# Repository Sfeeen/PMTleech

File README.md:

# 🚀 PMT Leech
#### A Parallel Memory Transactions Monitor

**PMT Leech** is a hardware + software tool that lets you monitor live memory accesses from a CPU to an external parallel memory chip.  
It streams transactions in real-time, while giving you full control over the system clock — allowing **pausing, stepping, and instruction-level debugging**.

---

## 🔧 When Should You Use PMT Leech?

PMT Leech is especially useful when working with **older electronic systems** that meet these two conditions:
- ✅ The system uses a **parallel memory chip** (like SRAM or EPROM)
- ✅ The CPU operates with an **external clock input**

---

## ⚙️ How It Works

By attaching PMT Leech to your memory chip (via clipper) and supplying your own clock signal to the CPU:
- You gain **live streaming** of memory transactions
- You can **pause or step** through firmware execution  
- You can **reverse engineer or debug** embedded firmware in a safe, controlled way

---

## 🧰 Hardware Overview

---

## 🖥️ Software Features

- 🧩 Configurable pinout: Supports 28, 30, or 32-pin chips
- 📡 Live recording of transactions (up to 70kHz)
- 🎨 Interactive memory viewer with color-coded highlights
- ⏱ Step by **clock** or **instruction**
- 🧠 Detect and label **foreign packets** (from other devices on the memory bus)
- 💾 Off-circuit memory read/write with chip socket

---

## 🎞️ Demo

---

## 📋 Requirements

### ✅ Memory Chip
- Parallel bus
- ≤ 8-bit data
- ≤ 18 address lines
- 5V compatible (or use 330Ω series resistors)

### ✅ CPU
- Must allow external clock input
- 5V compatible (or 330Ω resistors)

### ⚠️ Note on Timing
The CPU will be **underclocked** (e.g., 8 MHz → 50 kHz). This may affect peripherals like UART:
- Ex: 9600 baud becomes ~60 baud — comms may break.

---

## 🧲 In-Circuit Clip Options

- [📄 3M Test Clip Brochure (PDF)](research/in%20circuit%20connection%20to%20chips/Test%20Clip%20Brochure%203M.pdf)

---

## 🧠 Supported Memory Types

- EEPROM
- EPROM
- SRAM — **especially valuable** for volatile firmware systems

💡 Many older systems used **SRAM for firmware** due to speed advantages. PMT Leech lets you read these **volatile** setups **without desoldering**.

---

## 🔍 Example Use Cases

- **Bypass password protection**: Record firmware transactions during password validation and discover comparison logic or values.
- **Firmware reverse engineering**: Step through opcode streams and infer instruction flow.
- **Brownout glitching**: Control timing to inject faults and analyze behavior.
  - Related project: [Siemens Advanced Operator Panel](https://github.com/Sfeeen/Siemens-Advanced-Operator-Panel)

---

## 🛠️ Hardware Revisions

### PMT Leech v2 (Current)

### PMT Leech v1 (Development Stage)

---

##

📧 **Contact**: `svenonderbeke [at] hotmail [dot] com`  
More info to be added soon.

---

### ☕ Support

If you’d like to support the development of PMT Leech, you can donate via Ko-fi:

## 🧪 Version

**Current Version:** `PMT Leech v2`

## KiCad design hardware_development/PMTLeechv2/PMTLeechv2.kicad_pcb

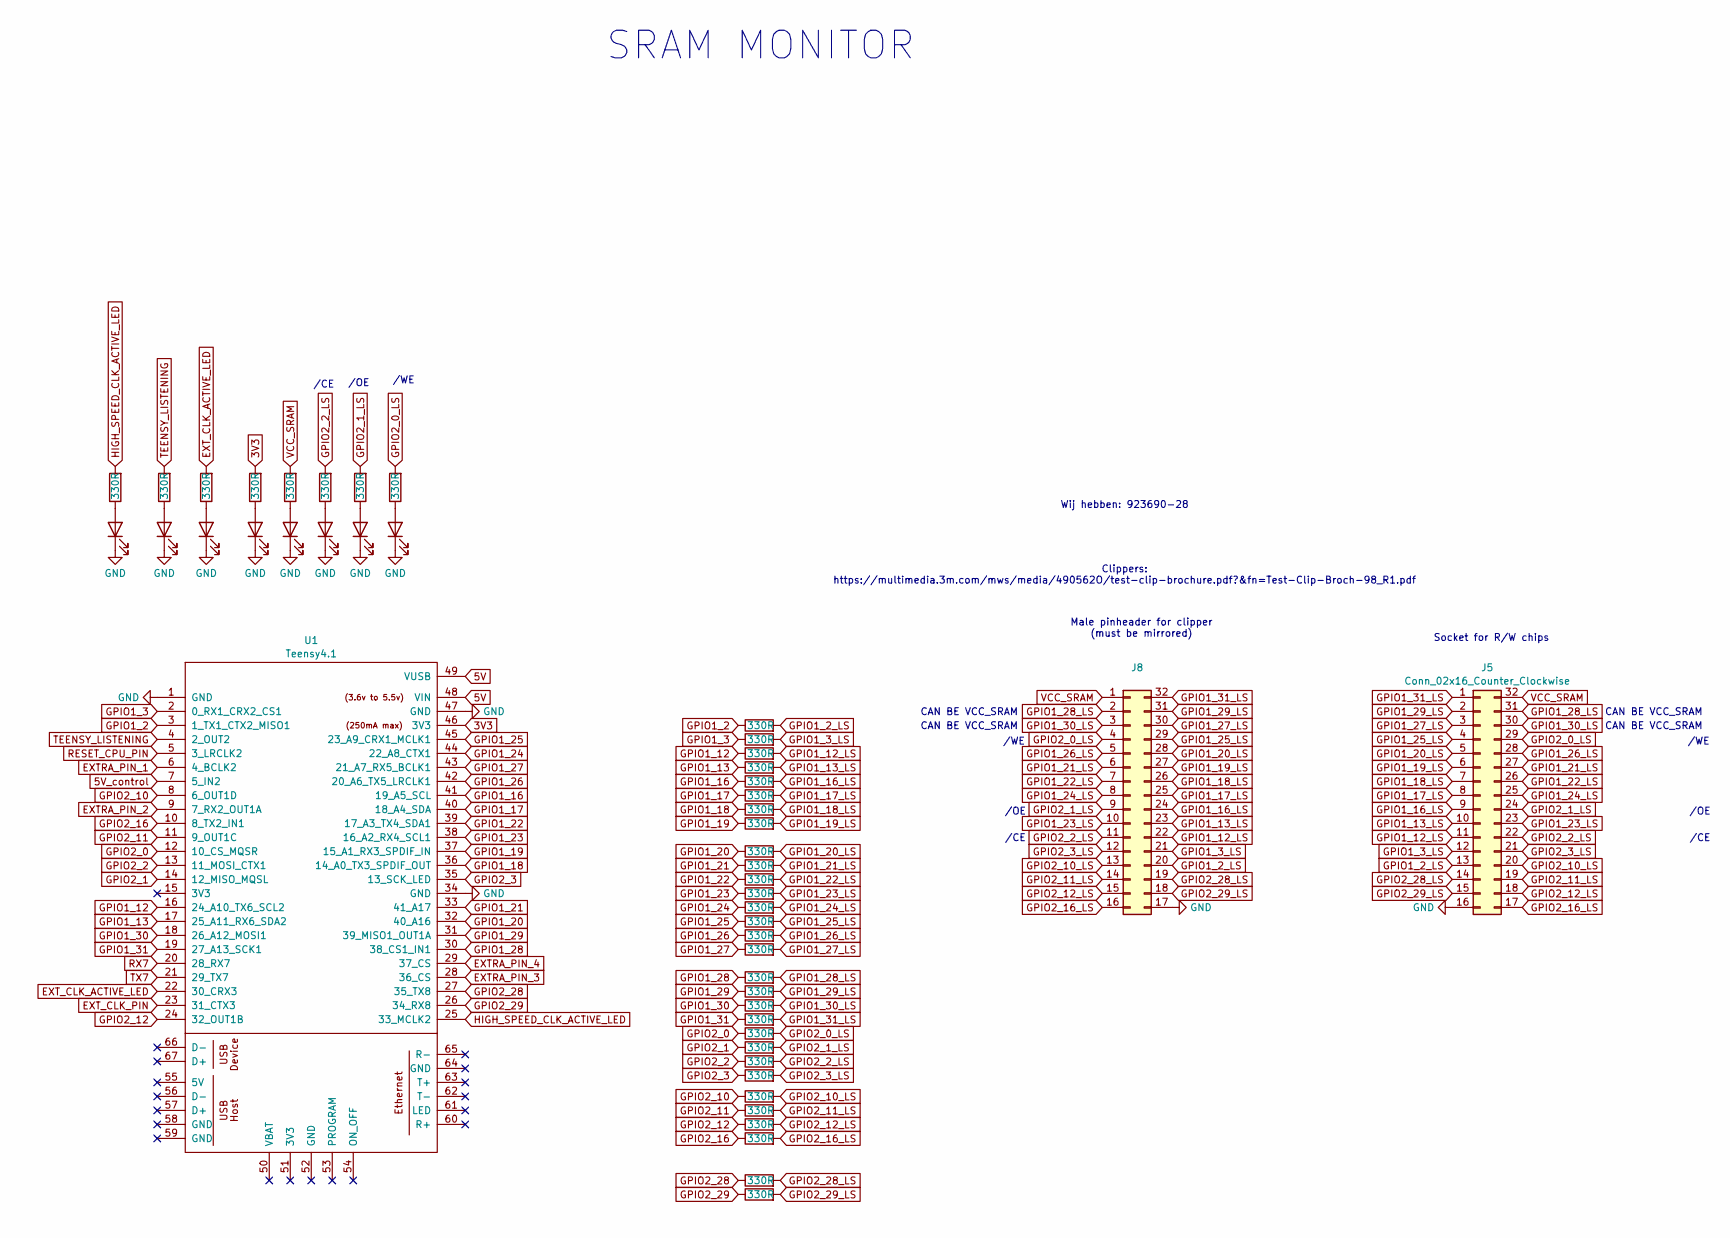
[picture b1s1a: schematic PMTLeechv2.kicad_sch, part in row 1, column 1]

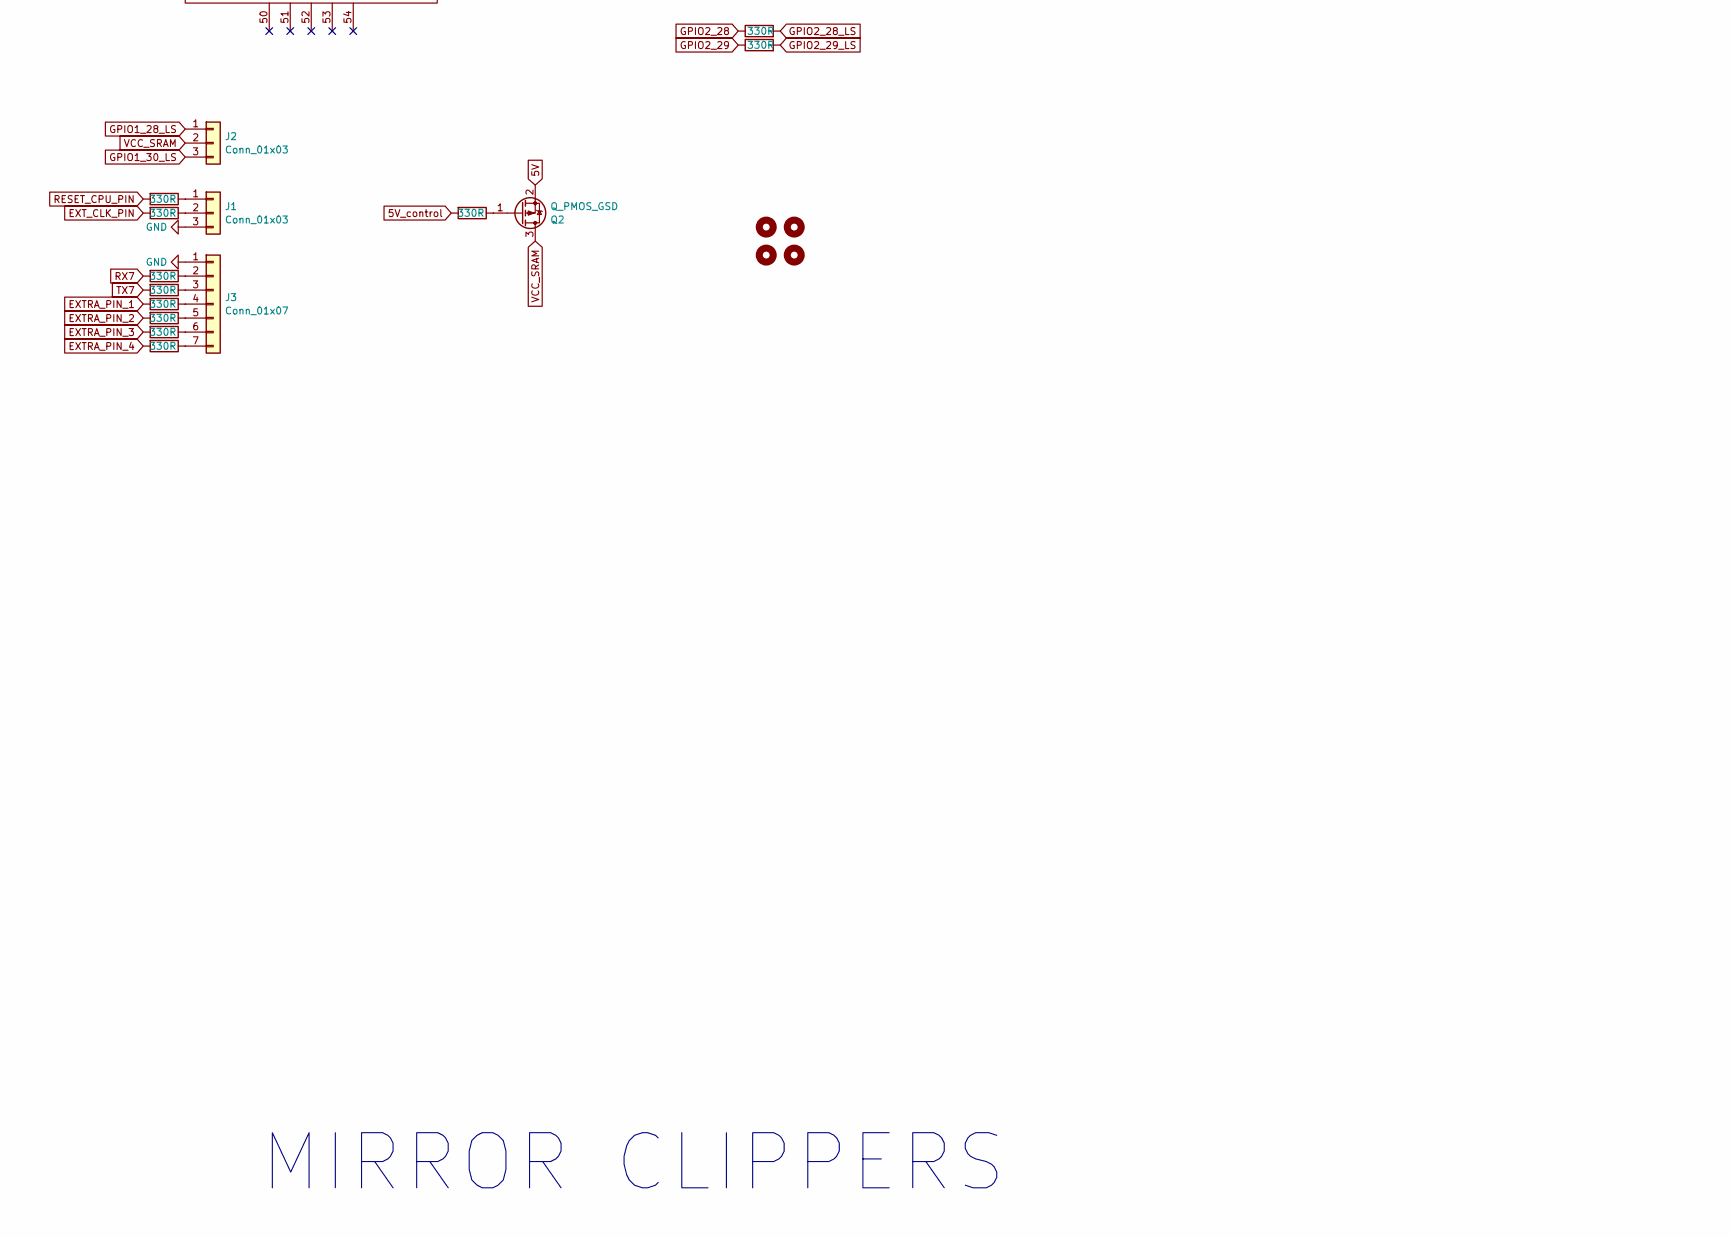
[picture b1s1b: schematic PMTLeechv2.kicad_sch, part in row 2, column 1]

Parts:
D1, D2, D3, D31, D32, D33, D34, D35: LED; LED_0805_2012Metric
H1, H2, H3, H4: MountingHole; MountingHole_3.2mm_M3
J1, J2: Conn_01x03; PinHeader_1x03_P2.54mm_Vertical
J3: Conn_01x07; PinHeader_1x07_P2.54mm_Vertical
J5: Conn_02x16_Counter_Clockwise; DIP-32_W15.24mm_Socket_LongPads
J8: Conn_02x16_Counter_Clockwise; PinHeader_2x16_P2.54mm_Vertical_clockwise
Q2: Q_PMOS_GSD; TSOT-23
R1, R2, R3, R4, R5, R6, R7, R8, R9, R10, R11, R12, R13, R14, R15, R16, R17, R18, R19, R20, R21, R22, R23, R24, R25, R26, R27, R28, R29, R30, R31, R32, R34, R35, R36, R37, R38, R39, R40, R41, R42, R43, R95, R96, R97, R98, R99: 330R; R_0603_1608Metric
U1: Teensy4.1; Teensy41

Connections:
3V3: R95.2, U1.46 (3V3)
5V: Q2.2 (S), U1.48 (VIN), U1.49 (VUSB)
5V_control: R30.2, U1.7 (5_IN2)
EXTRA_PIN_1: R37.2, U1.6 (4_BCLK2)
EXTRA_PIN_2: R42.2, U1.9 (7_RX2_OUT1A)
EXTRA_PIN_3: R38.2, U1.28 (36_CS)
EXTRA_PIN_4: R43.2, U1.29 (37_CS)
EXT_CLK_ACTIVE_LED: R34.2, U1.22 (30_CRX3)
EXT_CLK_PIN: R29.2, U1.23 (31_CTX3)
GND: D1.1 (K), D2.1 (K), D3.1 (K), D31.1 (K), D32.1 (K), D33.1 (K), D34.1 (K), D35.1 (K), J1.3, J3.1, J5.16, J8.17, U1.1 (GND), U1.34 (GND), U1.47 (GND)
GPIO1_2: R1.1, U1.3 (1_TX1_CTX2_MISO1)
GPIO1_2_LS: J5.13, J8.20, R1.2
GPIO1_3: R2.1, U1.2 (0_RX1_CRX2_CS1)
GPIO1_3_LS: J5.12, J8.21, R2.2
GPIO1_12: R3.1, U1.16 (24_A10_TX6_SCL2)
GPIO1_12_LS: J5.11, J8.22, R3.2
GPIO1_13: R4.1, U1.17 (25_A11_RX6_SDA2)
GPIO1_13_LS: J5.10, J8.23, R4.2
GPIO1_16: R5.1, U1.41 (19_A5_SCL)
GPIO1_16_LS: J5.9, J8.24, R5.2
GPIO1_17: R6.1, U1.40 (18_A4_SDA)
GPIO1_17_LS: J5.8, J8.25, R6.2
GPIO1_18: R7.1, U1.36 (14_A0_TX3_SPDIF_OUT)
GPIO1_18_LS: J5.7, J8.26, R7.2
GPIO1_19: R8.1, U1.37 (15_A1_RX3_SPDIF_IN)
GPIO1_19_LS: J5.6, J8.27, R8.2
GPIO1_20: R9.1, U1.32 (40_A16)
GPIO1_20_LS: J5.5, J8.28, R9.2
GPIO1_21: R10.1, U1.33 (41_A17)
GPIO1_21_LS: J5.27, J8.6, R10.2
GPIO1_22: R11.1, U1.39 (17_A3_TX4_SDA1)
GPIO1_22_LS: J5.26, J8.7, R11.2
GPIO1_23: R12.1, U1.38 (16_A2_RX4_SCL1)
GPIO1_23_LS: J5.23, J8.10, R12.2
GPIO1_24: R13.1, U1.44 (22_A8_CTX1)
GPIO1_24_LS: J5.25, J8.8, R13.2
GPIO1_25: R14.1, U1.45 (23_A9_CRX1_MCLK1)
GPIO1_25_LS: J5.4, J8.29, R14.2
GPIO1_26: R15.1, U1.42 (20_A6_TX5_LRCLK1)
GPIO1_26_LS: J5.28, J8.5, R15.2
GPIO1_27: R16.1, U1.43 (21_A7_RX5_BCLK1)
GPIO1_27_LS: J5.3, J8.30, R16.2
GPIO1_28: R17.1, U1.30 (38_CS1_IN1)
GPIO1_28_LS: J2.1, J5.31, J8.2, R17.2
GPIO1_29: R18.1, U1.31 (39_MISO1_OUT1A)
GPIO1_29_LS: J5.2, J8.31, R18.2
GPIO1_30: R19.1, U1.18 (26_A12_MOSI1)
GPIO1_30_LS: J2.3, J5.30, J8.3, R19.2
GPIO1_31: R20.1, U1.19 (27_A13_SCK1)
GPIO1_31_LS: J5.1, J8.32, R20.2
GPIO2_0: R21.1, U1.12 (10_CS_MQSR)
GPIO2_0_LS: J5.29, J8.4, R21.2, R99.2
GPIO2_1: R22.1, U1.14 (12_MISO_MQSL)
GPIO2_1_LS: J5.24, J8.9, R22.2, R98.2
GPIO2_2: R23.1, U1.13 (11_MOSI_CTX1)
GPIO2_2_LS: J5.22, J8.11, R23.2, R97.2
GPIO2_3: R24.1, U1.35 (13_SCK_LED)
GPIO2_3_LS: J5.21, J8.12, R24.2
GPIO2_10: R25.1, U1.8 (6_OUT1D)
GPIO2_10_LS: J5.20, J8.13, R25.2
GPIO2_11: R26.1, U1.11 (9_OUT1C)
GPIO2_11_LS: J5.19, J8.14, R26.2
GPIO2_12: R27.1, U1.24 (32_OUT1B)
GPIO2_12_LS: J5.18, J8.15, R27.2
GPIO2_16: R28.1, U1.10 (8_TX2_IN1)
GPIO2_16_LS: J5.17, J8.16, R28.2
GPIO2_28: R31.1, U1.27 (35_TX8)
GPIO2_28_LS: J5.14, J8.19, R31.2
GPIO2_29: R32.1, U1.26 (34_RX8)
GPIO2_29_LS: J5.15, J8.18, R32.2
HIGH_SPEED_CLK_ACTIVE_LED: R41.2, U1.25 (33_MCLK2)
unnamed: D1.2 (A), R34.1
unnamed: D2.2 (A), R35.1
unnamed: D3.2 (A), R41.1
unnamed: D31.2 (A), R95.1
unnamed: D32.2 (A), R96.1
unnamed: D33.2 (A), R97.1
unnamed: D34.2 (A), R98.1
unnamed: D35.2 (A), R99.1
unnamed: J1.1, R36.1
unnamed: J1.2, R29.1
unnamed: J3.2, R39.1
unnamed: J3.3, R40.1
unnamed: J3.4, R37.1
unnamed: J3.5, R42.1
unnamed: J3.6, R38.1
unnamed: J3.7, R43.1
unnamed: Q2.1 (G), R30.1
RESET_CPU_PIN: R36.2, U1.5 (3_LRCLK2)
RX7: R39.2, U1.20 (28_RX7)
TEENSY_LISTENING: R35.2, U1.4 (2_OUT2)
TX7: R40.2, U1.21 (29_TX7)
VCC_SRAM: J2.2, J5.32, J8.1, Q2.3 (D), R96.2

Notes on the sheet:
Wij hebben: 923690-28
CAN BE VCC_SRAM
/CE
/WE
SRAM MONITOR
MIRROR CLIPPERS
Clippers: https://multimedia.3m.com/mws/media/490562O/test-clip-brochure.pdf?&fn=Test-Clip-Broch-98_R1.pdf
Socket for R/W chips
/OE
Male pinheader for clipper (must be mirrored)

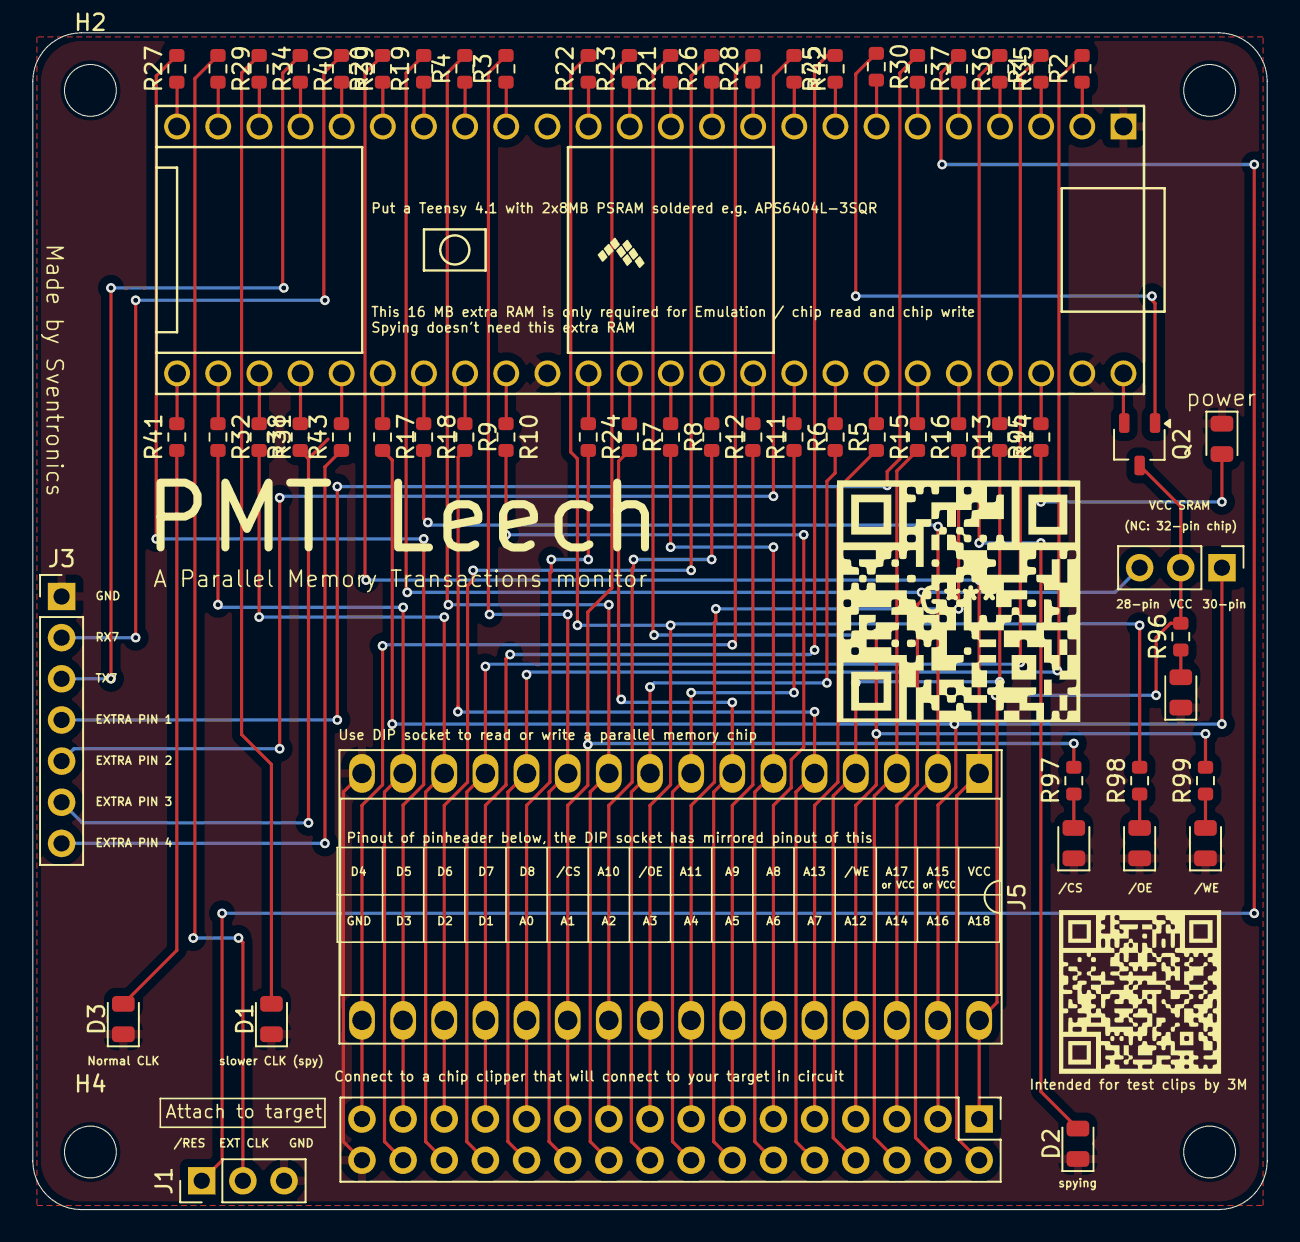
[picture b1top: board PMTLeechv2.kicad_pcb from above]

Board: 2 copper layers, 76.2 x 72.6 mm, 66 parts (0 on the bottom side), 93 nets.

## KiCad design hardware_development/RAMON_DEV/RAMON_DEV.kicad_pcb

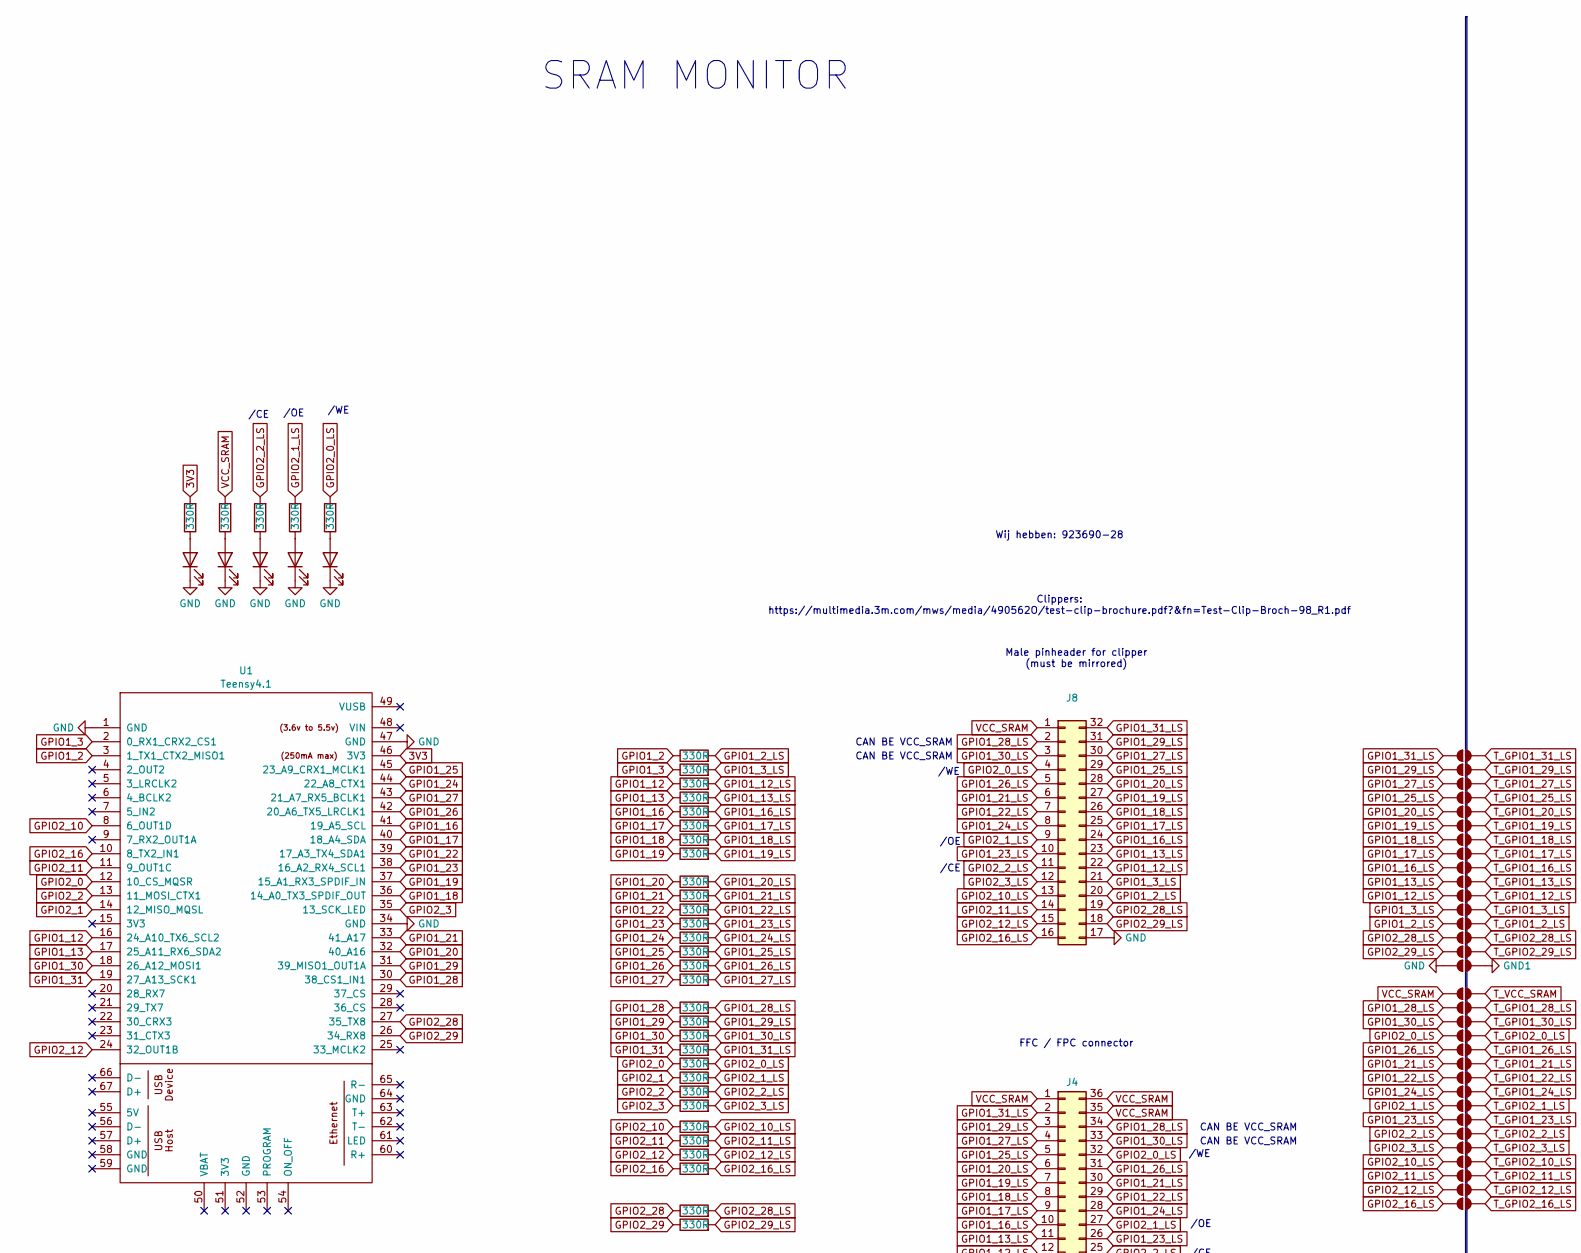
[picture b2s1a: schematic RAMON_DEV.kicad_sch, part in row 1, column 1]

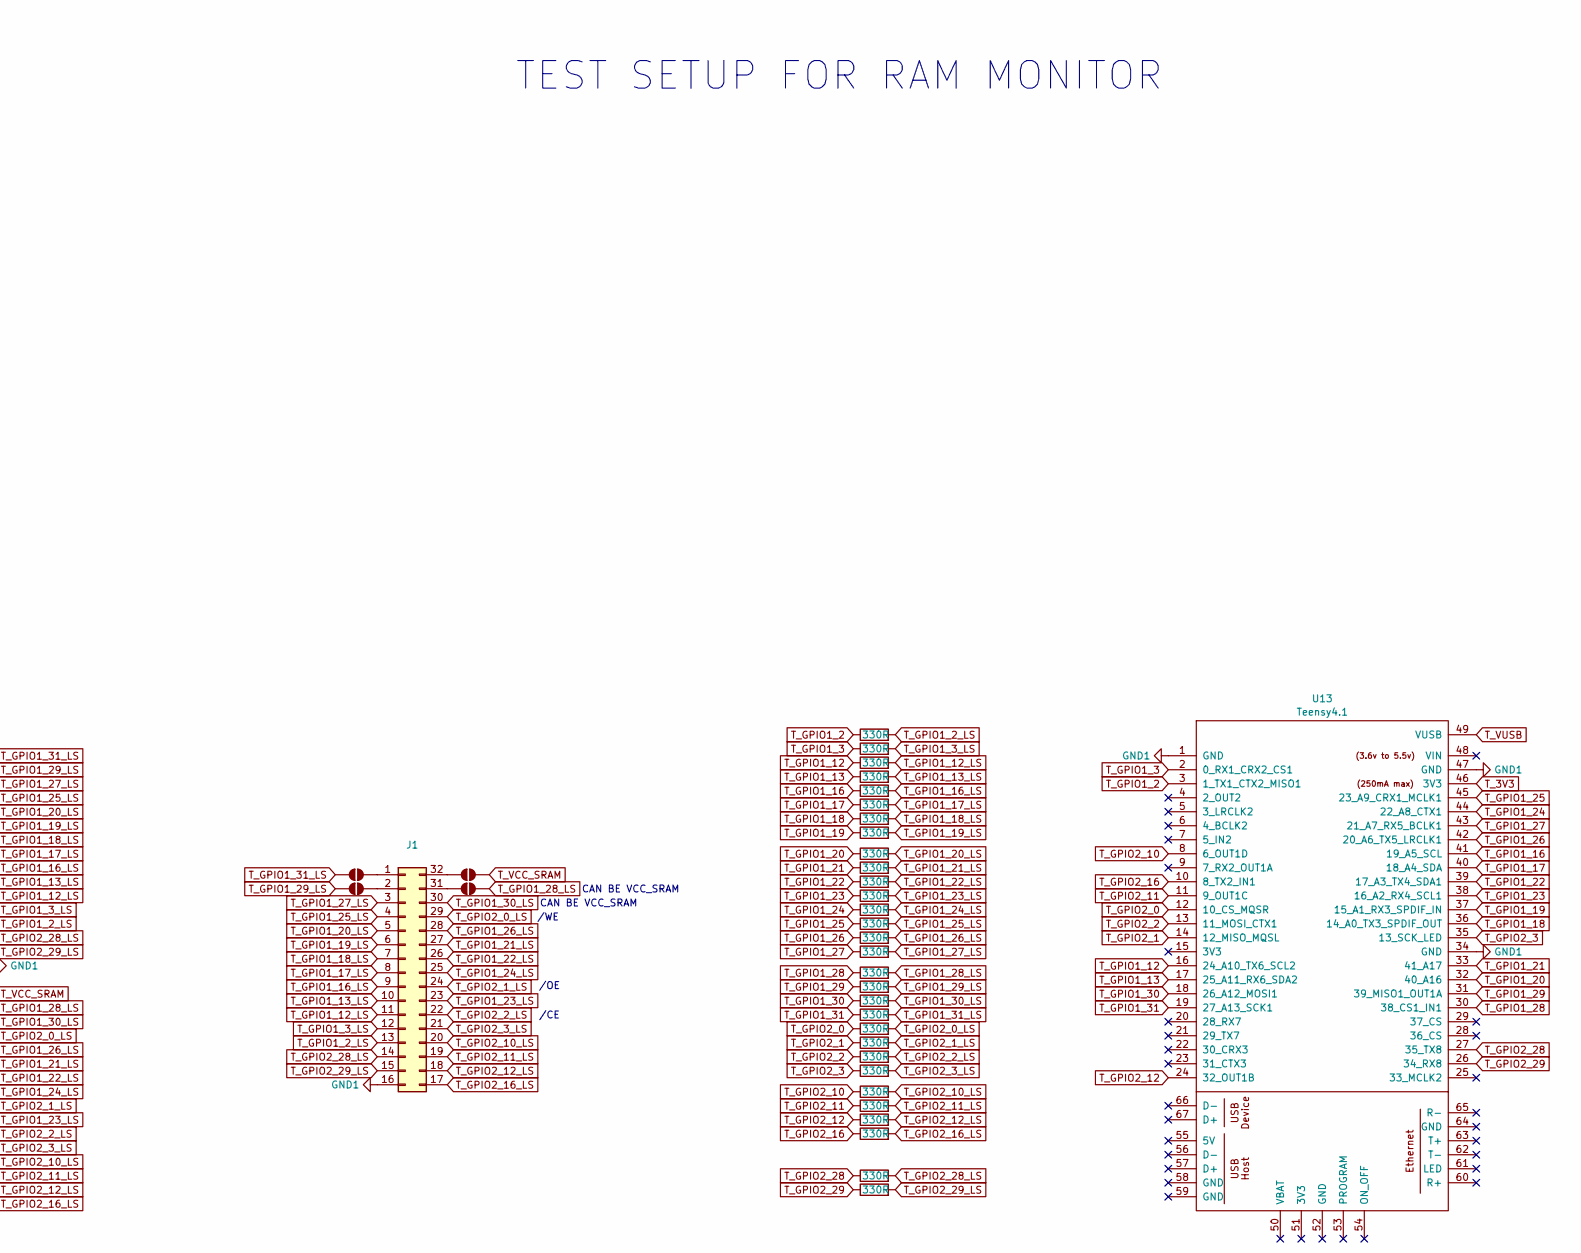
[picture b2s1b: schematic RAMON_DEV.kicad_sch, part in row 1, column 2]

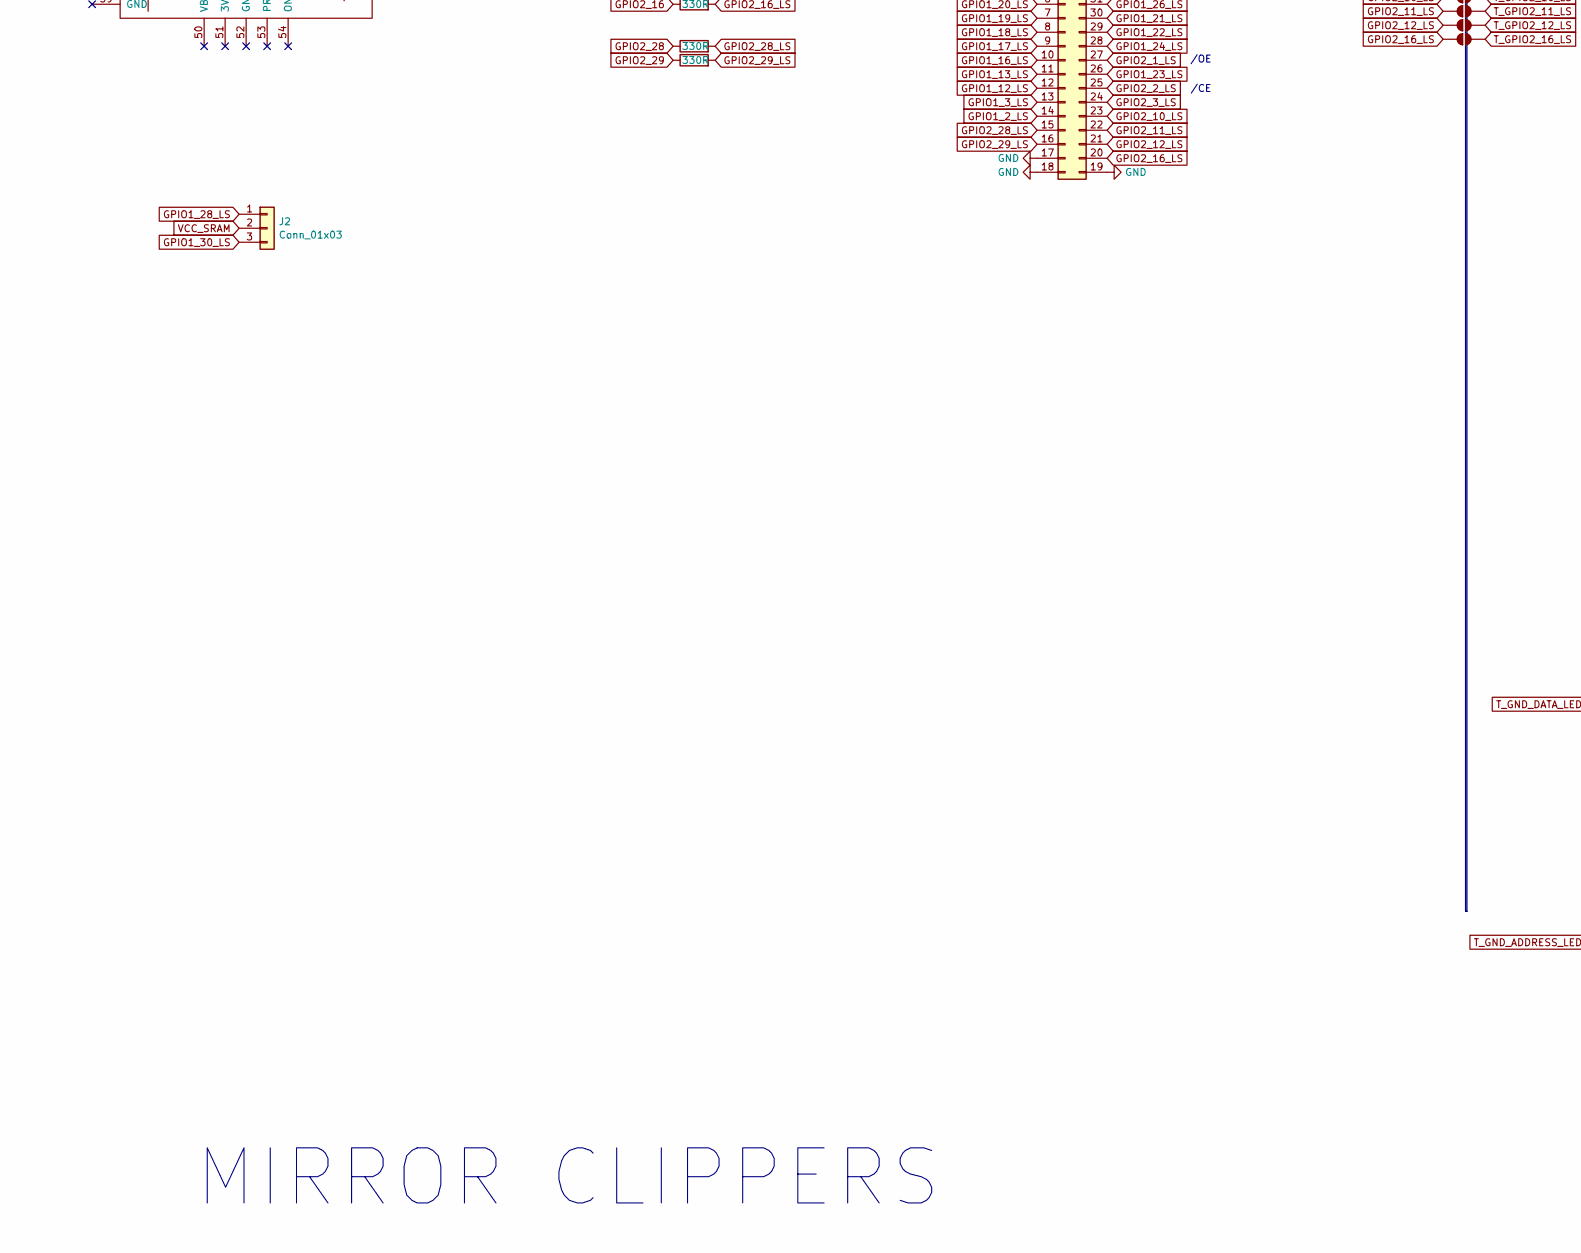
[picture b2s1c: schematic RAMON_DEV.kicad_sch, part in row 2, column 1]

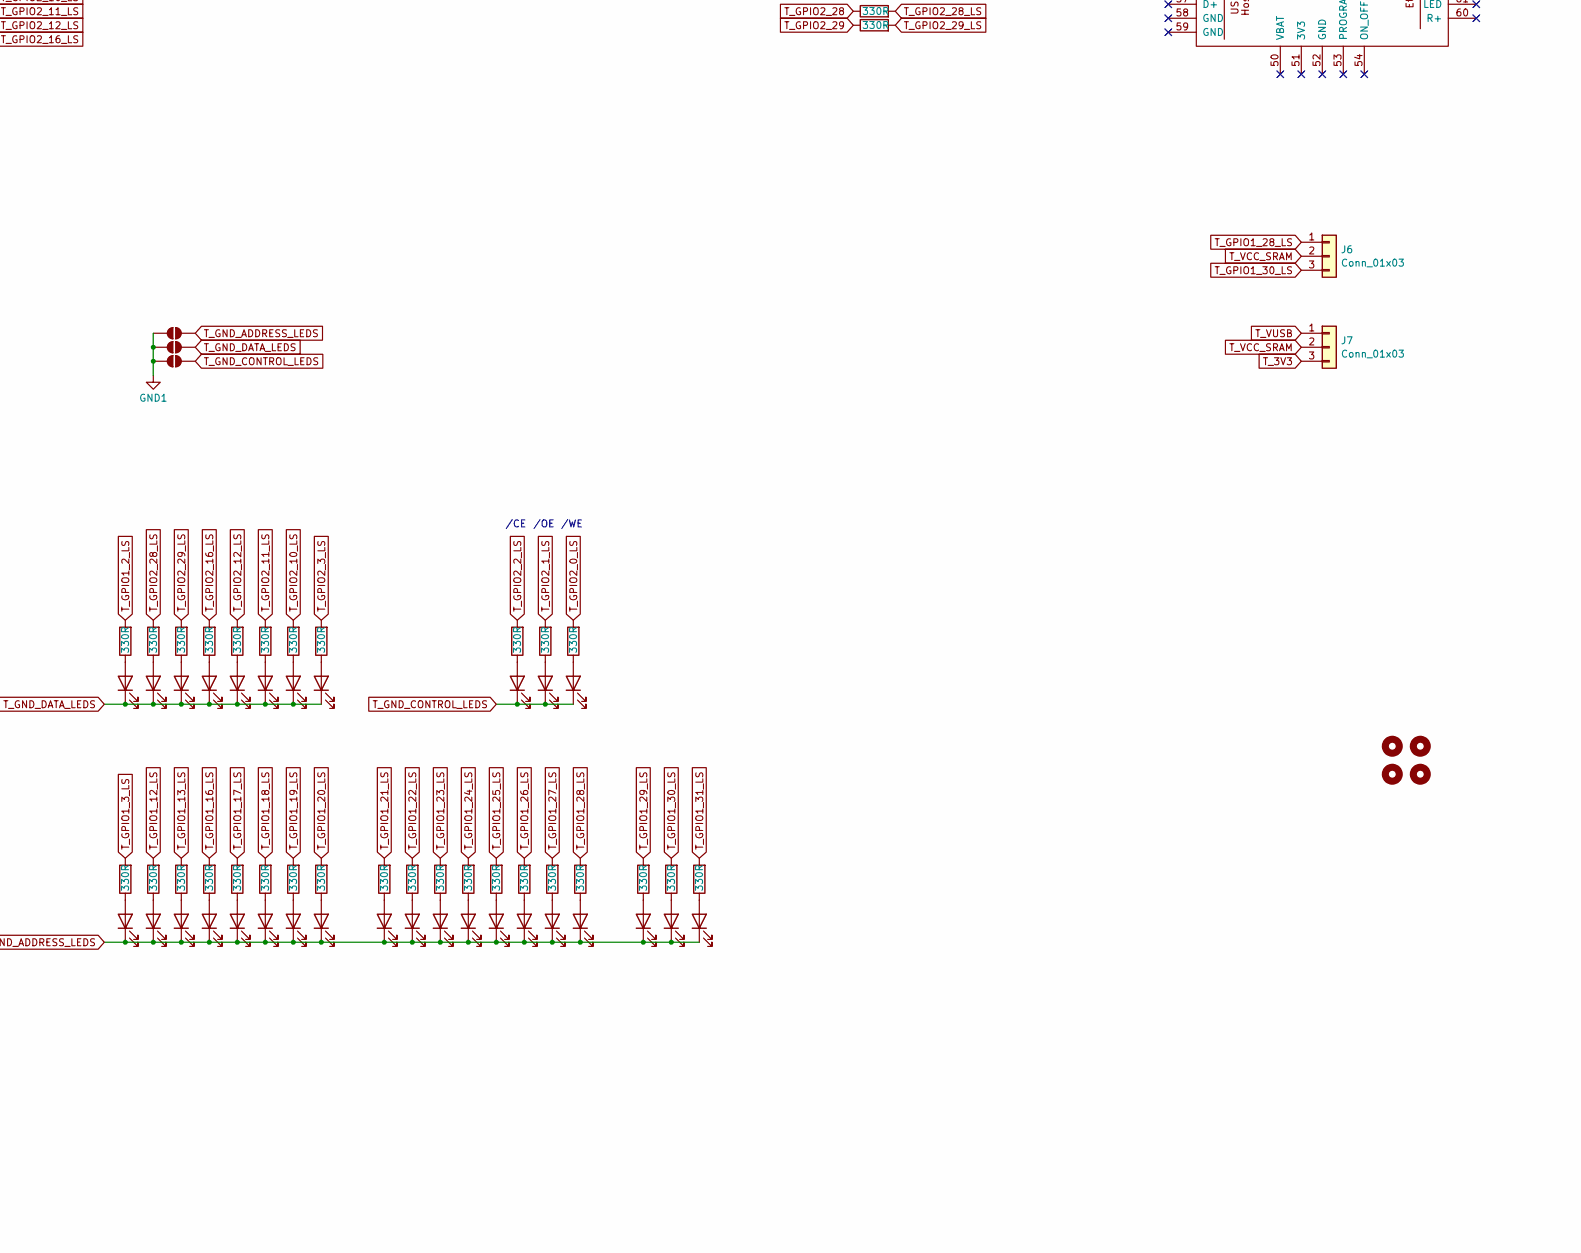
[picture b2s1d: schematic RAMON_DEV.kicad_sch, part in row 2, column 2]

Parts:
D1, D2, D3, D4, D5, D6, D7, D8, D9, D10, D11, D12, D13, D14, D15, D16, D17, D18, D19, D20, D21, D22, D23, D24, D25, D26, D27, D28, D29, D30, D31, D32, D33, D34, D35: LED; LED_0805_2012Metric
H1, H2, H3, H4: MountingHole; MountingHole_3.2mm_M3
J1: Conn_02x16_Counter_Clockwise; DIP-32_W15.24mm_Socket
J2, J6, J7: Conn_01x03; PinHeader_1x03_P2.54mm_Vertical
J4: Conn_02x18_Counter_Clockwise; Hirose_FH12-36S-0.5SH_1x36-1MP_P0.50mm_Horizontal
J8: Conn_02x16_Counter_Clockwise; PinHeader_2x16_P2.54mm_Vertical_clockwise
JP1, JP2, JP3, JP4, JP5, JP6, JP7, JP8, JP9, JP10, JP11, JP12, JP13, JP14, JP15, JP16, JP17, JP18, JP19, JP20, JP21, JP22, JP23, JP24, JP25, JP26, JP27, JP28, JP29, JP30, JP31, JP32, JP33, JP34, JP35, JP38, JP41, JP42, JP43: SolderJumper_2_Open; SolderJumper-2_P1.3mm_Open_TrianglePad1.0x1.5mm
R1, R2, R3, R4, R5, R6, R7, R8, R9, R10, R11, R12, R13, R14, R15, R16, R17, R18, R19, R20, R21, R22, R23, R24, R25, R26, R27, R28, R31, R32, R33, R34, R35, R36, R37, R38, R39, R40, R41, R42, R43, R44, R45, R46, R47, R48, R49, R50, R51, R52, R53, R54, R55, R56, R57, R58, R59, R60, R63, R64, R65, R66, R67, R68, R69, R70, R71, R72, R73, R74, R75, R76, R77, R78, R79, R80, R81, R82, R83, R84, R85, R86, R87, R88, R89, R90, R91, R92, R93, R94, R95, R96, R97, R98, R99: 330R; R_0805_2012Metric
U1, U13: Teensy4.1; Teensy41

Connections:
3V3: R95.2, U1.46 (3V3)
GND: D31.1 (K), D32.1 (K), D33.1 (K), D34.1 (K), D35.1 (K), J4.17, J4.18, J4.19, J8.17, JP17.1 (A), U1.1 (GND), U1.34 (GND), U1.47 (GND)
GND1: J1.16, JP17.2 (B), JP41.1 (A), JP42.1 (A), JP43.1 (A), U13.1 (GND), U13.34 (GND), U13.47 (GND)
GPIO1_2: R1.1, U1.3 (1_TX1_CTX2_MISO1)
GPIO1_2_LS: J4.14, J8.20, JP14.1 (A), R1.2
GPIO1_3: R2.1, U1.2 (0_RX1_CRX2_CS1)
GPIO1_3_LS: J4.13, J8.21, JP13.1 (A), R2.2
GPIO1_12: R3.1, U1.16 (24_A10_TX6_SCL2)
GPIO1_12_LS: J4.12, J8.22, JP12.1 (A), R3.2
GPIO1_13: R4.1, U1.17 (25_A11_RX6_SDA2)
GPIO1_13_LS: J4.11, J8.23, JP11.1 (A), R4.2
GPIO1_16: R5.1, U1.41 (19_A5_SCL)
GPIO1_16_LS: J4.10, J8.24, JP10.1 (A), R5.2
GPIO1_17: R6.1, U1.40 (18_A4_SDA)
GPIO1_17_LS: J4.9, J8.25, JP9.1 (A), R6.2
GPIO1_18: R7.1, U1.36 (14_A0_TX3_SPDIF_OUT)
GPIO1_18_LS: J4.8, J8.26, JP8.1 (A), R7.2
GPIO1_19: R8.1, U1.37 (15_A1_RX3_SPDIF_IN)
GPIO1_19_LS: J4.7, J8.27, JP7.1 (A), R8.2
GPIO1_20: R9.1, U1.32 (40_A16)
GPIO1_20_LS: J4.6, J8.28, JP6.1 (A), R9.2
GPIO1_21: R10.1, U1.33 (41_A17)
GPIO1_21_LS: J4.30, J8.6, JP24.1 (A), R10.2
GPIO1_22: R11.1, U1.39 (17_A3_TX4_SDA1)
GPIO1_22_LS: J4.29, J8.7, JP25.1 (A), R11.2
GPIO1_23: R12.1, U1.38 (16_A2_RX4_SCL1)
GPIO1_23_LS: J4.26, J8.10, JP28.1 (A), R12.2
GPIO1_24: R13.1, U1.44 (22_A8_CTX1)
GPIO1_24_LS: J4.28, J8.8, JP26.1 (A), R13.2
GPIO1_25: R14.1, U1.45 (23_A9_CRX1_MCLK1)
GPIO1_25_LS: J4.5, J8.29, JP5.1 (A), R14.2
GPIO1_26: R15.1, U1.42 (20_A6_TX5_LRCLK1)
GPIO1_26_LS: J4.31, J8.5, JP23.1 (A), R15.2
GPIO1_27: R16.1, U1.43 (21_A7_RX5_BCLK1)
GPIO1_27_LS: J4.4, J8.30, JP4.1 (A), R16.2
GPIO1_28: R17.1, U1.30 (38_CS1_IN1)
GPIO1_28_LS: J2.1, J4.34, J8.2, JP20.1 (A), R17.2
GPIO1_29: R18.1, U1.31 (39_MISO1_OUT1A)
GPIO1_29_LS: J4.3, J8.31, JP3.1 (A), R18.2
GPIO1_30: R19.1, U1.18 (26_A12_MOSI1)
GPIO1_30_LS: J2.3, J4.33, J8.3, JP21.1 (A), R19.2
GPIO1_31: R20.1, U1.19 (27_A13_SCK1)
GPIO1_31_LS: J4.2, J8.32, JP2.1 (A), R20.2
GPIO2_0: R21.1, U1.12 (10_CS_MQSR)
GPIO2_0_LS: J4.32, J8.4, JP22.1 (A), R21.2, R99.2
GPIO2_1: R22.1, U1.14 (12_MISO_MQSL)
GPIO2_1_LS: J4.27, J8.9, JP27.1 (A), R22.2, R98.2
GPIO2_2: R23.1, U1.13 (11_MOSI_CTX1)
GPIO2_2_LS: J4.25, J8.11, JP29.1 (A), R23.2, R97.2
GPIO2_3: R24.1, U1.35 (13_SCK_LED)
GPIO2_3_LS: J4.24, J8.12, JP30.1 (A), R24.2
GPIO2_10: R25.1, U1.8 (6_OUT1D)
GPIO2_10_LS: J4.23, J8.13, JP31.1 (A), R25.2
GPIO2_11: R26.1, U1.11 (9_OUT1C)
GPIO2_11_LS: J4.22, J8.14, JP32.1 (A), R26.2
GPIO2_12: R27.1, U1.24 (32_OUT1B)
GPIO2_12_LS: J4.21, J8.15, JP33.1 (A), R27.2
GPIO2_16: R28.1, U1.10 (8_TX2_IN1)
GPIO2_16_LS: J4.20, J8.16, JP34.1 (A), R28.2
GPIO2_28: R31.1, U1.27 (35_TX8)
GPIO2_28_LS: J4.15, J8.19, JP15.1 (A), R31.2
GPIO2_29: R32.1, U1.26 (34_RX8)
GPIO2_29_LS: J4.16, J8.18, JP16.1 (A), R32.2
unnamed: D1.2 (A), R65.1
unnamed: D2.2 (A), R66.1
unnamed: D3.2 (A), R67.1
unnamed: D4.2 (A), R68.1
unnamed: D5.2 (A), R69.1
unnamed: D6.2 (A), R70.1
unnamed: D7.2 (A), R71.1
unnamed: D8.2 (A), R72.1
unnamed: D9.2 (A), R73.1
unnamed: D10.2 (A), R74.1
unnamed: D11.2 (A), R75.1
unnamed: D12.2 (A), R76.1
unnamed: D13.2 (A), R77.1
unnamed: D14.2 (A), R78.1
unnamed: D15.2 (A), R79.1
unnamed: D16.2 (A), R80.1
unnamed: D17.2 (A), R81.1
unnamed: D18.2 (A), R82.1
unnamed: D19.2 (A), R83.1
unnamed: D20.2 (A), R84.1
unnamed: D21.2 (A), R85.1
unnamed: D22.2 (A), R86.1
unnamed: D23.2 (A), R87.1
unnamed: D24.2 (A), R88.1
unnamed: D25.2 (A), R89.1
unnamed: D26.2 (A), R90.1
unnamed: D27.2 (A), R91.1
unnamed: D28.2 (A), R92.1
unnamed: D29.2 (A), R93.1
unnamed: D30.2 (A), R94.1
unnamed: D31.2 (A), R95.1
unnamed: D32.2 (A), R96.1
unnamed: D33.2 (A), R97.1
unnamed: D34.2 (A), R98.1
unnamed: D35.2 (A), R99.1
unnamed: J1.1, JP18.2 (B)
unnamed: J1.2, JP1.2 (B)
unnamed: J1.31, JP38.1 (A)
unnamed: J1.32, JP35.1 (A)
OE: U1.25 (33_MCLK2)
T_3V3: J7.3, U13.46 (3V3)
T_GND_ADDRESS_LEDS: D1.1 (K), D10.1 (K), D11.1 (K), D12.1 (K), D13.1 (K), D14.1 (K), D15.1 (K), D16.1 (K), D17.1 (K), D18.1 (K), D19.1 (K), D20.1 (K), D21.1 (K), D22.1 (K), D23.1 (K), D24.1 (K), D25.1 (K), D26.1 (K), D27.1 (K), JP41.2 (B)
T_GND_CONTROL_LEDS: D28.1 (K), D29.1 (K), D30.1 (K), JP43.2 (B)
T_GND_DATA_LEDS: D2.1 (K), D3.1 (K), D4.1 (K), D5.1 (K), D6.1 (K), D7.1 (K), D8.1 (K), D9.1 (K), JP42.2 (B)
T_GPIO1_2: R33.1, U13.3 (1_TX1_CTX2_MISO1)
T_GPIO1_2_LS: J1.13, JP14.2 (B), R33.2, R66.2
T_GPIO1_3: R34.1, U13.2 (0_RX1_CRX2_CS1)
T_GPIO1_3_LS: J1.12, JP13.2 (B), R34.2, R65.2
T_GPIO1_12: R35.1, U13.16 (24_A10_TX6_SCL2)
T_GPIO1_12_LS: J1.11, JP12.2 (B), R35.2, R74.2
T_GPIO1_13: R36.1, U13.17 (25_A11_RX6_SDA2)
T_GPIO1_13_LS: J1.10, JP11.2 (B), R36.2, R75.2
T_GPIO1_16: R37.1, U13.41 (19_A5_SCL)
T_GPIO1_16_LS: J1.9, JP10.2 (B), R37.2, R76.2
T_GPIO1_17: R38.1, U13.40 (18_A4_SDA)
T_GPIO1_17_LS: J1.8, JP9.2 (B), R38.2, R77.2
T_GPIO1_18: R39.1, U13.36 (14_A0_TX3_SPDIF_OUT)
T_GPIO1_18_LS: J1.7, JP8.2 (B), R39.2, R78.2
T_GPIO1_19: R40.1, U13.37 (15_A1_RX3_SPDIF_IN)
T_GPIO1_19_LS: J1.6, JP7.2 (B), R40.2, R79.2
T_GPIO1_20: R41.1, U13.32 (40_A16)
T_GPIO1_20_LS: J1.5, JP6.2 (B), R41.2, R80.2
T_GPIO1_21: R42.1, U13.33 (41_A17)
T_GPIO1_21_LS: J1.27, JP24.2 (B), R42.2, R81.2
T_GPIO1_22: R43.1, U13.39 (17_A3_TX4_SDA1)
T_GPIO1_22_LS: J1.26, JP25.2 (B), R43.2, R82.2
T_GPIO1_23: R44.1, U13.38 (16_A2_RX4_SCL1)
T_GPIO1_23_LS: J1.23, JP28.2 (B), R44.2, R83.2
T_GPIO1_24: R45.1, U13.44 (22_A8_CTX1)
T_GPIO1_24_LS: J1.25, JP26.2 (B), R45.2, R84.2
T_GPIO1_25: R46.1, U13.45 (23_A9_CRX1_MCLK1)
T_GPIO1_25_LS: J1.4, JP5.2 (B), R46.2, R85.2
T_GPIO1_26: R47.1, U13.42 (20_A6_TX5_LRCLK1)
T_GPIO1_26_LS: J1.28, JP23.2 (B), R47.2, R86.2
T_GPIO1_27: R48.1, U13.43 (21_A7_RX5_BCLK1)
T_GPIO1_27_LS: J1.3, JP4.2 (B), R48.2, R87.2
T_GPIO1_28: R49.1, U13.30 (38_CS1_IN1)
T_GPIO1_28_LS: J6.1, JP20.2 (B), JP38.2 (B), R49.2, R88.2
T_GPIO1_29: R50.1, U13.31 (39_MISO1_OUT1A)
T_GPIO1_29_LS: JP1.1 (A), JP3.2 (B), R50.2, R89.2
T_GPIO1_30: R51.1, U13.18 (26_A12_MOSI1)
T_GPIO1_30_LS: J1.30, J6.3, JP21.2 (B), R51.2, R90.2
T_GPIO1_31: R52.1, U13.19 (27_A13_SCK1)
T_GPIO1_31_LS: JP2.2 (B), JP18.1 (A), R52.2, R91.2
T_GPIO2_0: R53.1, U13.12 (10_CS_MQSR)
T_GPIO2_0_LS: J1.29, JP22.2 (B), R53.2, R94.2
T_GPIO2_1: R54.1, U13.14 (12_MISO_MQSL)
T_GPIO2_1_LS: J1.24, JP27.2 (B), R54.2, R93.2
T_GPIO2_2: R55.1, U13.13 (11_MOSI_CTX1)
T_GPIO2_2_LS: J1.22, JP29.2 (B), R55.2, R92.2
T_GPIO2_3: R56.1, U13.35 (13_SCK_LED)
T_GPIO2_3_LS: J1.21, JP30.2 (B), R56.2, R73.2
T_GPIO2_10: R57.1, U13.8 (6_OUT1D)
T_GPIO2_10_LS: J1.20, JP31.2 (B), R57.2, R72.2
T_GPIO2_11: R58.1, U13.11 (9_OUT1C)
T_GPIO2_11_LS: J1.19, JP32.2 (B), R58.2, R71.2
T_GPIO2_12: R59.1, U13.24 (32_OUT1B)
T_GPIO2_12_LS: J1.18, JP33.2 (B), R59.2, R70.2
T_GPIO2_16: R60.1, U13.10 (8_TX2_IN1)
T_GPIO2_16_LS: J1.17, JP34.2 (B), R60.2, R69.2
T_GPIO2_28: R63.1, U13.27 (35_TX8)
T_GPIO2_28_LS: J1.14, JP15.2 (B), R63.2, R67.2
T_GPIO2_29: R64.1, U13.26 (34_RX8)
T_GPIO2_29_LS: J1.15, JP16.2 (B), R64.2, R68.2
T_OE: U13.25 (33_MCLK2)
T_VCC_SRAM: J6.2, J7.2, JP19.2 (B), JP35.2 (B)
T_VUSB: J7.1, U13.49 (VUSB)
VCC_SRAM: J2.2, J4.1, J4.35, J4.36, J8.1, JP19.1 (A), R96.2

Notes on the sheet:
CAN BE VCC_SRAM
Wij hebben: 923690-28
/OE
/WE
/CE
SRAM MONITOR
FFC / FPC connector
MIRROR CLIPPERS
Clippers: https://multimedia.3m.com/mws/media/490562O/test-clip-brochure.pdf?&fn=Test-Clip-Broch-98_R1.pdf
TEST SETUP FOR RAM MONITOR
Male pinheader for clipper (must be mirrored)
